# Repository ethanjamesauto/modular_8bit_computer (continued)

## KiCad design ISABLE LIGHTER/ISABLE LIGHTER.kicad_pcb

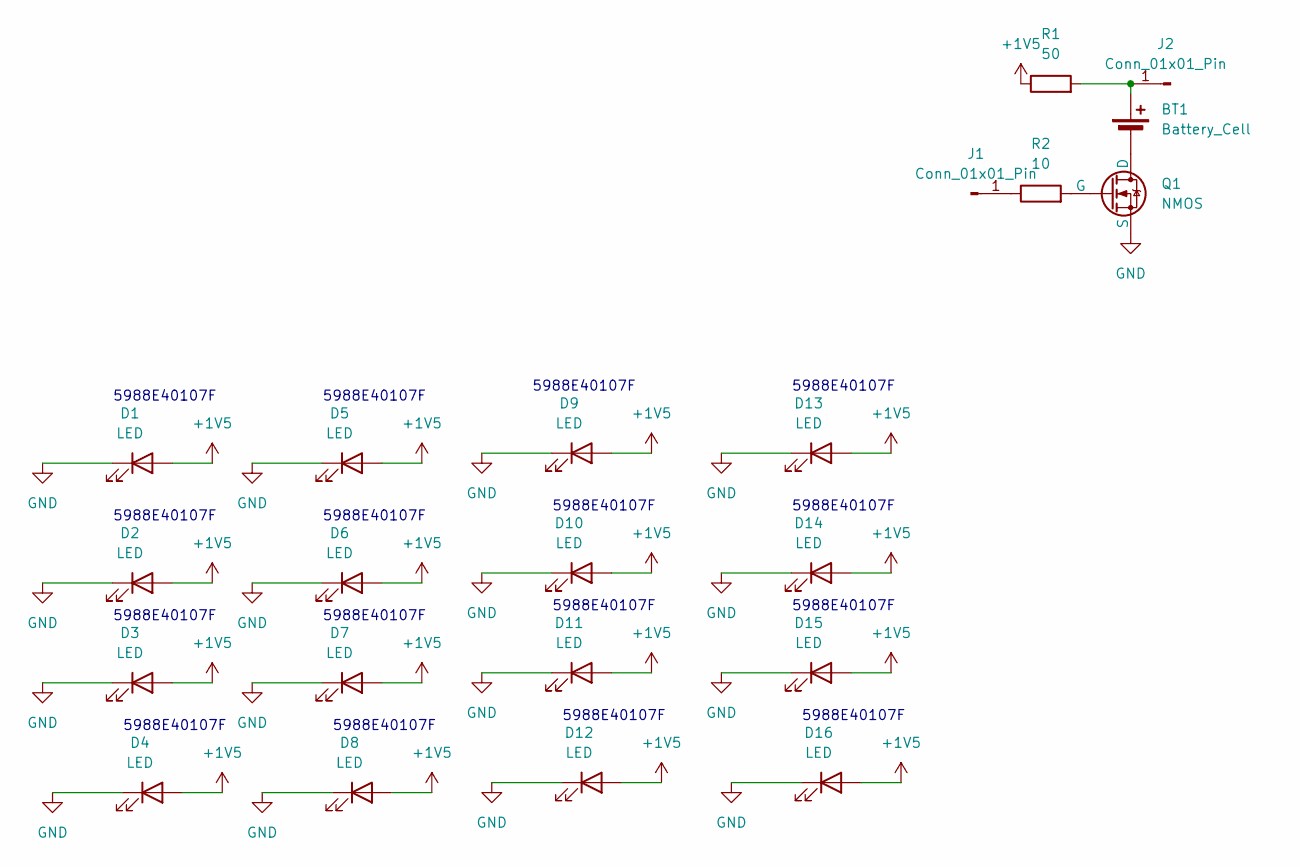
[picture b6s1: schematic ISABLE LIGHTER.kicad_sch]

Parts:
BT1: Battery_Cell; BatteryHolder_Keystone_3008_1x2450
D1, D2, D3, D4, D5, D6, D7, D8, D9, D10, D11, D12, D13, D14, D15, D16: LED; R_0603_1608Metric_Pad0.98x0.95mm_HandSolder
J1, J2: Conn_01x01_Pin; PinHeader_1x01_P2.54mm_Vertical
Q1: NMOS; SOT-323_SC-70_Handsoldering
R1: 50; R_0603_1608Metric_Pad0.98x0.95mm_HandSolder
R2: 10; R_0603_1608Metric_Pad0.98x0.95mm_HandSolder

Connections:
+1V5: D1.2 (A), D2.2 (A), D3.2 (A), D4.2 (A), D5.2 (A), D6.2 (A), D7.2 (A), D8.2 (A), D9.2 (A), D10.2 (A), D11.2 (A), D12.2 (A), D13.2 (A), D14.2 (A), D15.2 (A), D16.2 (A), R1.1
GND: D1.1 (K), D2.1 (K), D3.1 (K), D4.1 (K), D5.1 (K), D6.1 (K), D7.1 (K), D8.1 (K), D9.1 (K), D10.1 (K), D11.1 (K), D12.1 (K), D13.1 (K), D14.1 (K), D15.1 (K), D16.1 (K), Q1.3 (S)
unnamed: BT1.1 (+), J2.1, R1.2
unnamed: BT1.2 (-), Q1.1 (D)
unnamed: J1.1, R2.1
unnamed: Q1.2 (G), R2.2

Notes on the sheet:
5988E40107F

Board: 2 copper layers, 22 parts (1 on the bottom side), 6 nets, no tracks yet.

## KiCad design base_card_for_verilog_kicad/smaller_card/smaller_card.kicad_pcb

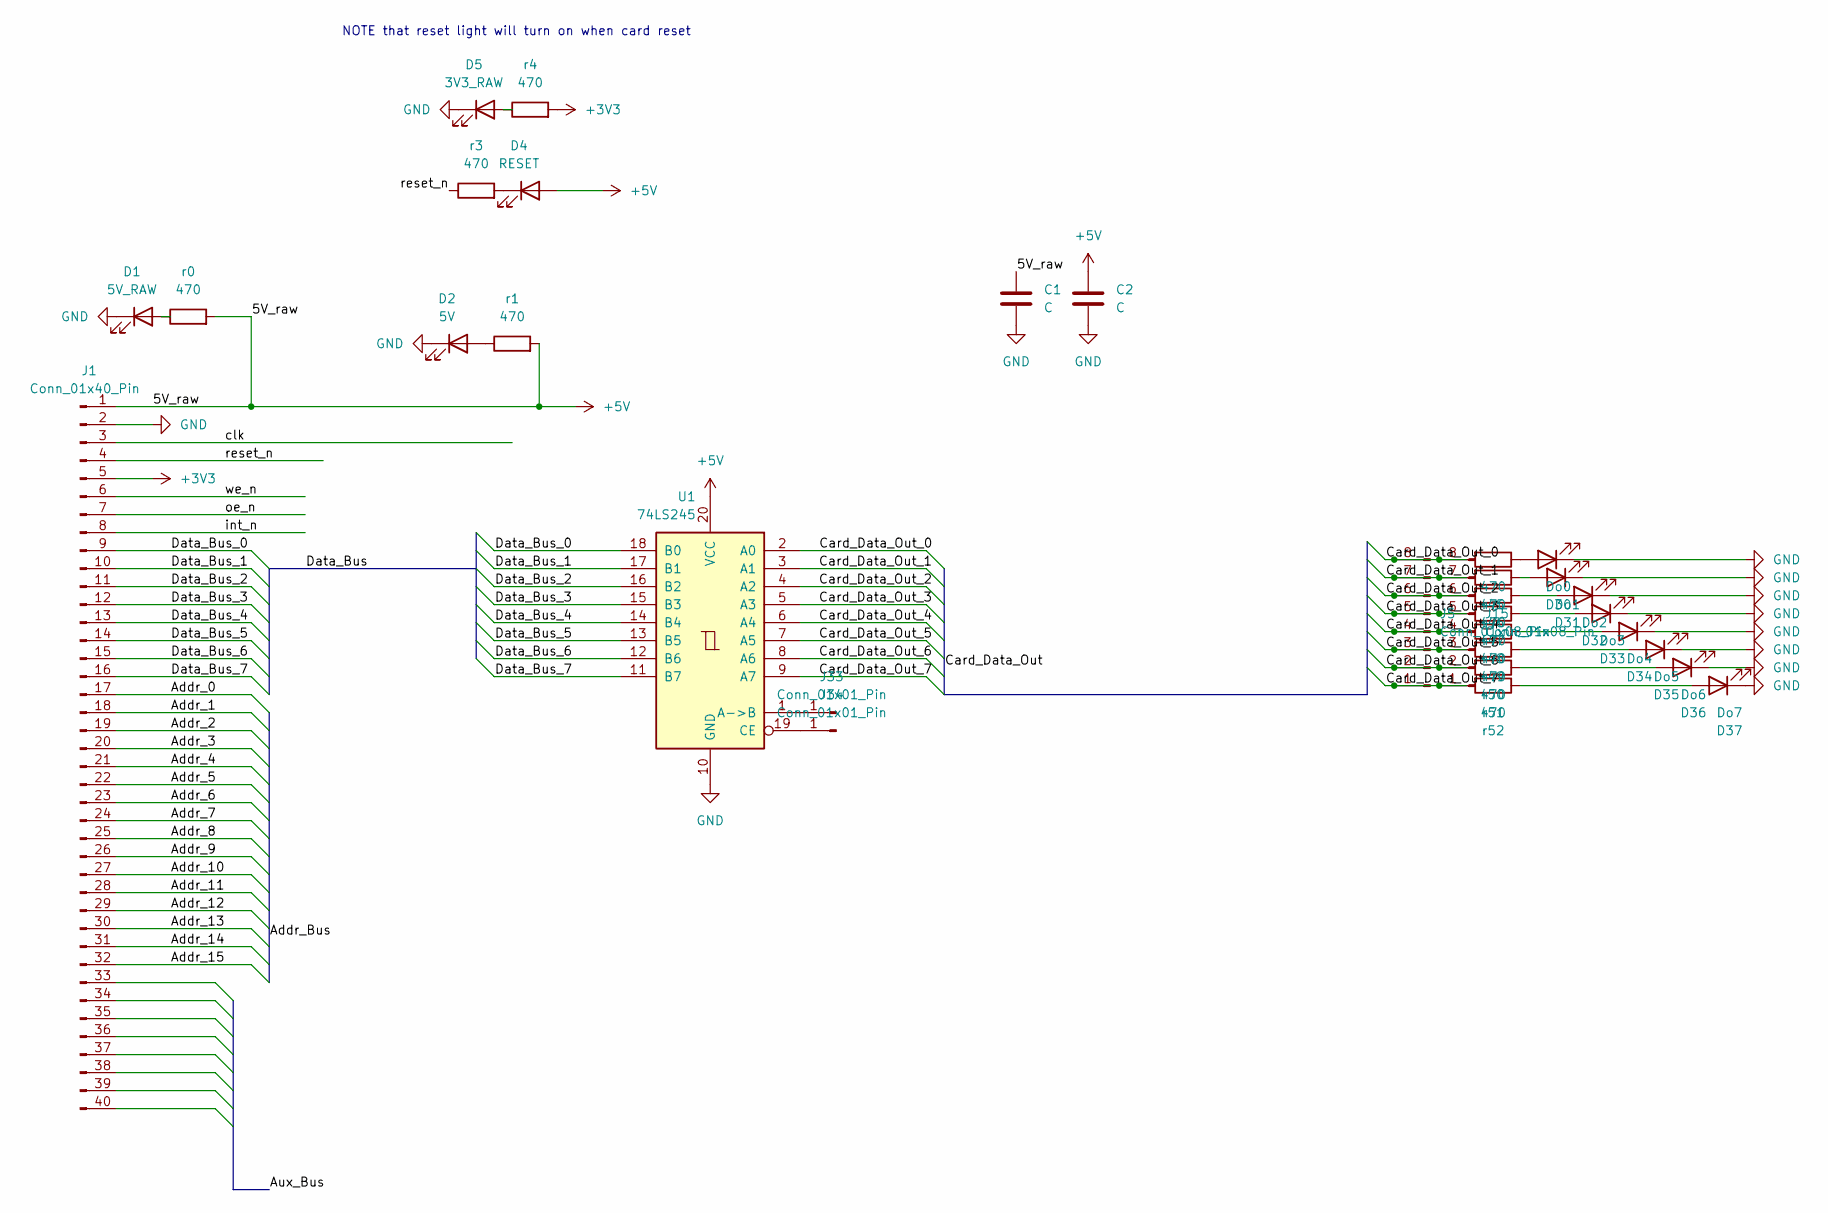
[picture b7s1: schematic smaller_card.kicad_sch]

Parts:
C1, C2: C; C_1206_3216Metric
D1: 5V_RAW; LED_0603_1608Metric_Pad1.05x0.95mm_HandSolder
D2: 5V; LED_0603_1608Metric_Pad1.05x0.95mm_HandSolder
D4: RESET; LED_0603_1608Metric_Pad1.05x0.95mm_HandSolder
D5: 3V3_RAW; LED_0603_1608Metric_Pad1.05x0.95mm_HandSolder
D30: Do0; LED_0603_1608Metric_Pad1.05x0.95mm_HandSolder
D31: Do1; LED_0603_1608Metric_Pad1.05x0.95mm_HandSolder
D32: Do2; LED_0603_1608Metric_Pad1.05x0.95mm_HandSolder
D33: Do3; LED_0603_1608Metric_Pad1.05x0.95mm_HandSolder
D34: Do4; LED_0603_1608Metric_Pad1.05x0.95mm_HandSolder
D35: Do5; LED_0603_1608Metric_Pad1.05x0.95mm_HandSolder
D36: Do6; LED_0603_1608Metric_Pad1.05x0.95mm_HandSolder
D37: Do7; LED_0603_1608Metric_Pad1.05x0.95mm_HandSolder
J1: Conn_01x40_Pin; PinHeader_1x40_P2.54mm_Horizontal
J5, J15: Conn_01x08_Pin; PinHeader_1x08_P2.54mm_Vertical
J33, J34: Conn_01x01_Pin; PinHeader_1x01_P2.54mm_Vertical
U1: 74LS245; DIP-20_W7.62mm_Socket
r0, r1, r3, r4, r45, r46, r47, r48, r49, r50, r51, r52: 470; R_0603_1608Metric_Pad0.98x0.95mm_HandSolder

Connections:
+3V3: J1.5, r4.2
+5V: C1.1, C2.1, D4.2 (A), J1.1, U1.20 (VCC), r0.2, r1.2; also elsewhere on the board
/Addr_0: J1.17
/Addr_1: J1.18
/Addr_2: J1.19
/Addr_3: J1.20
/Addr_4: J1.21
/Addr_5: J1.22
/Addr_6: J1.23
/Addr_7: J1.24
/Addr_8: J1.25
/Addr_9: J1.26
/Addr_10: J1.27
/Addr_11: J1.28
/Addr_12: J1.29
/Addr_13: J1.30
/Addr_14: J1.31
/Addr_15: J1.32
/Card_Data_Out_0: J5.8, J15.8, U1.2 (A0), r45.2
/Card_Data_Out_1: J5.7, J15.7, U1.3 (A1), r46.2
/Card_Data_Out_2: J5.6, J15.6, U1.4 (A2), r47.2
/Card_Data_Out_3: J5.5, J15.5, U1.5 (A3), r48.2
/Card_Data_Out_4: J5.4, J15.4, U1.6 (A4), r49.2
/Card_Data_Out_5: J5.3, J15.3, U1.7 (A5), r50.2
/Card_Data_Out_6: J5.2, J15.2, U1.8 (A6), r51.2
/Card_Data_Out_7: J5.1, J15.1, U1.9 (A7), r52.2
/Data_Bus_0: J1.9, U1.18 (B0)
/Data_Bus_1: J1.10, U1.17 (B1)
/Data_Bus_2: J1.11, U1.16 (B2)
/Data_Bus_3: J1.12, U1.15 (B3)
/Data_Bus_4: J1.13, U1.14 (B4)
/Data_Bus_5: J1.14, U1.13 (B5)
/Data_Bus_6: J1.15, U1.12 (B6)
/Data_Bus_7: J1.16, U1.11 (B7)
/clk: J1.3
/int_n: J1.8
/oe_n: J1.7
/reset_n: J1.4, r3.1
/we_n: J1.6
GND: C1.2, C2.2, D1.1 (K), D2.1 (K), D5.1 (K), D30.1 (K), D31.1 (K), D32.1 (K), D33.1 (K), D34.1 (K), D35.1 (K), D36.1 (K), D37.1 (K), J1.2, U1.10 (GND)
unnamed: D1.2 (A), r0.1
unnamed: D2.2 (A), r1.1
unnamed: D4.1 (K), r3.2
unnamed: D5.2 (A), r4.1
unnamed: D30.2 (A), r45.1
unnamed: D31.2 (A), r46.1
unnamed: D32.2 (A), r47.1
unnamed: D33.2 (A), r48.1
unnamed: D34.2 (A), r49.1
unnamed: D35.2 (A), r50.1
unnamed: D36.2 (A), r51.1
unnamed: D37.2 (A), r52.1
unnamed: J33.1, U1.1 (A->B)
unnamed: J34.1, U1.19 (CE)

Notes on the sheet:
NOTE that reset light will turn on when card reset

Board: 2 copper layers, 33 parts (0 on the bottom side), 34 nets, no tracks yet.

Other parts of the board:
5V_rsns1: 1; R_1206_3216Metric

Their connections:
+5V: 5V_rsns1.2; also elsewhere on the board

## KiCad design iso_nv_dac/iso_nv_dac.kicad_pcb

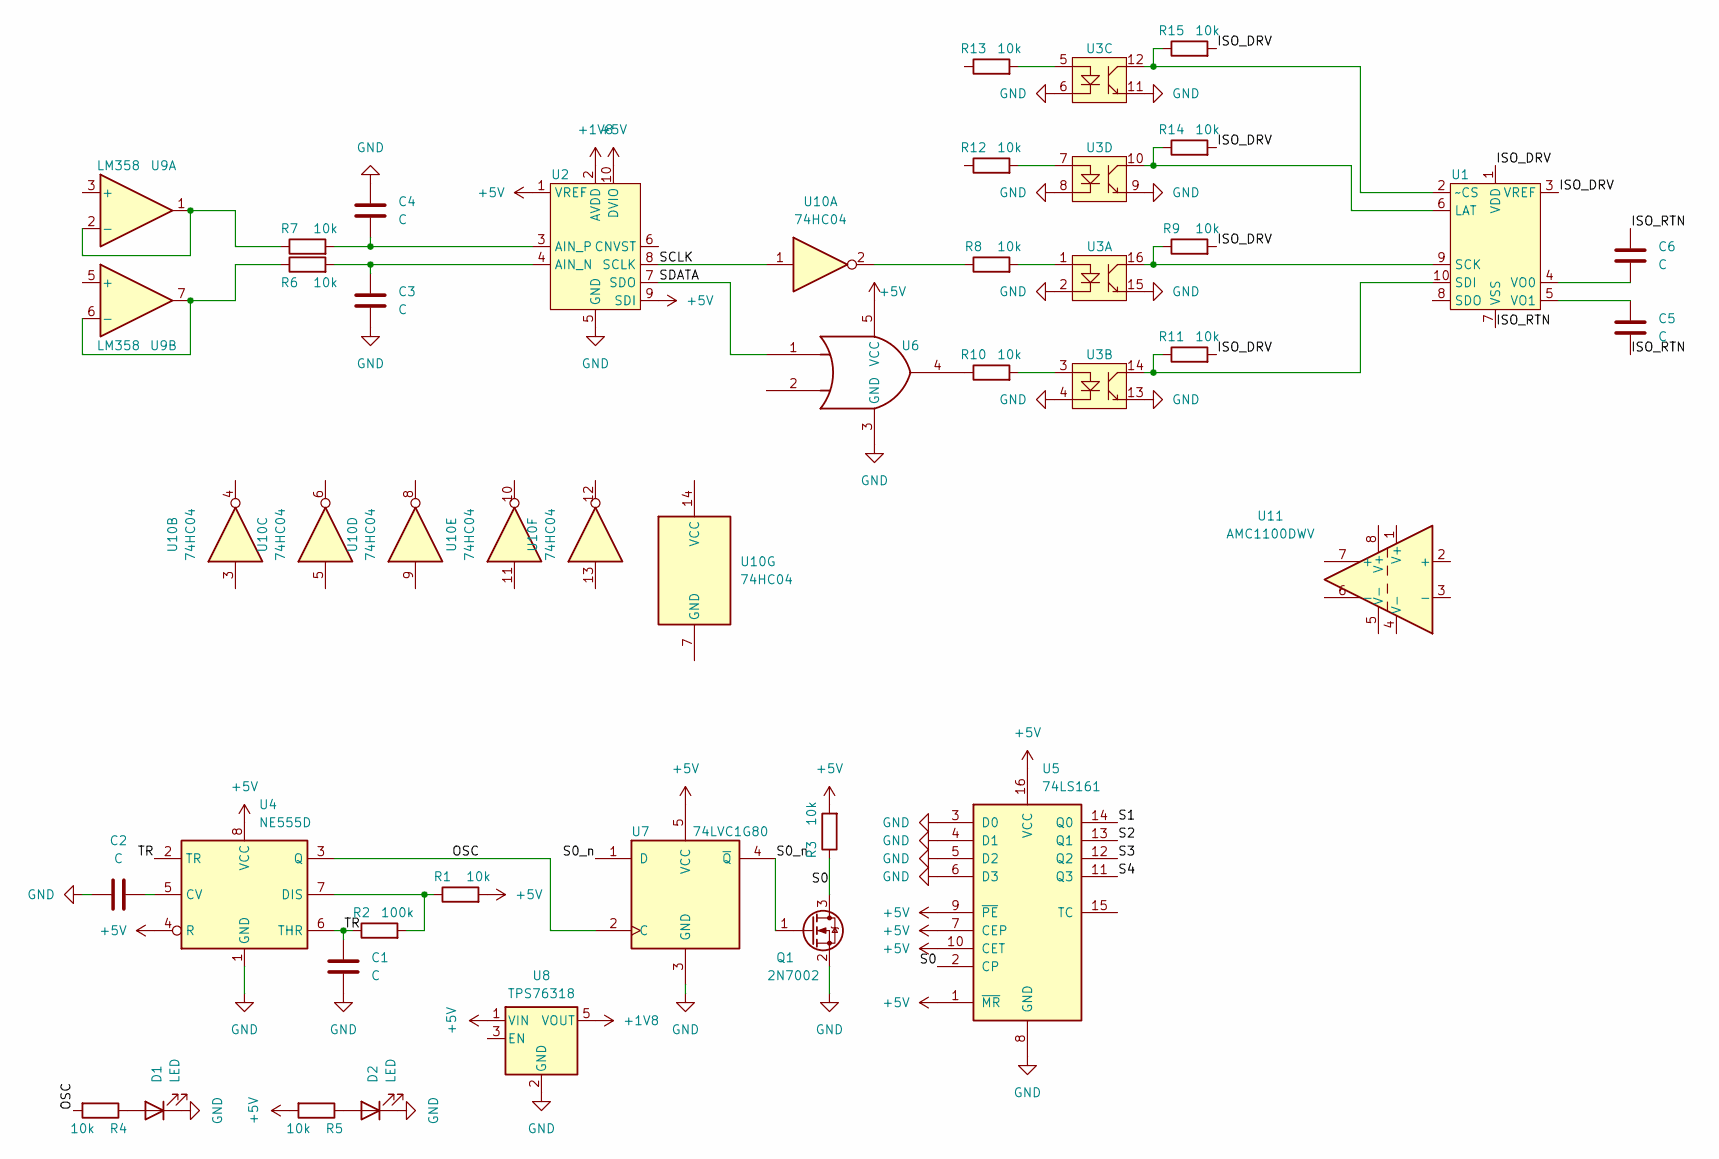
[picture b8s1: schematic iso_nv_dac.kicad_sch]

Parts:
C1, C2, C3, C4, C5, C6: C; C_0603_1608Metric_Pad1.08x0.95mm_HandSolder
D1, D2: LED; LED_0603_1608Metric_Pad1.05x0.95mm_HandSolder
Q1: 2N7002; SOT-23
R1, R3, R4, R5, R6, R7, R8, R9, R10, R11, R12, R13, R14, R15: 10k; R_0603_1608Metric_Pad0.98x0.95mm_HandSolder
R2: 100k; R_0603_1608Metric_Pad0.98x0.95mm_HandSolder
U1: MSOP-10_3x3mm_P0.5mm
U2: MCP33141D; MSOP-10_3x3mm_P0.5mm
U3: SOIC-16_4.55x10.3mm_P1.27mm
U4: NE555D; SOIC-8_3.9x4.9mm_P1.27mm
U5: 74LS161; SOIC-16_4.55x10.3mm_P1.27mm
U6: 74LVC1G32; SOT-23-5_HandSoldering
U7: 74LVC1G80; SOT-23-5_HandSoldering
U8: TPS76318; SOT-23-5
U9: LM358; SOIC-8_3.9x4.9mm_P1.27mm
U10: 74HC04; SOIC-14_3.9x8.7mm_P1.27mm
U11: AMC1100DWV; SOIC-8_7.5x5.85mm_P1.27mm

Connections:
+1V8: U2.2 (AVDD), U8.5 (VOUT)
+5V: R1.2, R3.2, R5.2, U2.1 (VREF), U2.9 (SDI), U2.10 (DVIO), U4.4 (R), U4.8 (VCC), U5.1 (~MR), U5.7 (CEP), U5.9 (~PE), U5.10 (CET), U5.16 (VCC), U6.5 (VCC), U7.5 (VCC), U8.1 (VIN)
/ISO_DRV: R9.2, R11.2, R14.2, R15.2, U1.1 (VDD), U1.3 (VREF)
/ISO_RTN: C5.1, C6.2, U1.7 (VSS)
/OSC: R4.2, U4.3 (Q), U7.2 (C)
/S0: Q1.3 (D), R3.1, U5.2 (CP)
/S0_n: Q1.1 (G), U7.1 (D), U7.4 (~Q)
/S1: U5.14 (Q0)
/S2: U5.13 (Q1)
/S3: U5.12 (Q2)
/S4: U5.11 (Q3)
/SCLK: U2.8 (SCLK), U10.1
/SDATA: U2.7 (SDO), U6.1
/TR: C1.1, R2.1, U4.2 (TR), U4.6 (THR)
GND: C1.2, C2.1, C3.1, C4.2, D1.1 (K), D2.1 (K), Q1.2 (S), U2.5 (GND), U3.2, U3.4, U3.6, U3.8, U3.9, U3.11, U3.13, U3.15, U4.1 (GND), U5.3 (D0), U5.4 (D1), U5.5 (D2), U5.6 (D3), U5.8 (GND), U6.3 (GND), U7.3 (GND), U8.2 (GND)
unnamed: D1.2 (A), R4.1
unnamed: D2.2 (A), R5.1
unnamed: R8.1, U10.2
unnamed: R8.2, U3.1
unnamed: R10.1, U6.4
unnamed: R10.2, U3.3
unnamed: R12.2, U3.7
unnamed: R13.2, U3.5
unnamed: R14.1, U1.6 (LAT), U3.10
unnamed: R9.1, U1.9 (SCK), U3.16
unnamed: R11.1, U1.10 (SDI), U3.14
unnamed: C6.1, U1.4 (VO0)
unnamed: C5.2, U1.5 (VO1)
unnamed: R15.1, U1.2 (~CS), U3.12
unnamed: C3.2, R6.2, U2.4 (AIN_N)
unnamed: C4.1, R7.2, U2.3 (AIN_P)
unnamed: C2.2, U4.5 (CV)
unnamed: R1.1, R2.2, U4.7 (DIS)
unnamed: R7.1, U9.1, U9.2 (-)
unnamed: R6.1, U9.6 (-), U9.7

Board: 2 copper layers, 35 parts (0 on the bottom side), 31 nets, no tracks yet.
